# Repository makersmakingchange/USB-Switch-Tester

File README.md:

# USB SWITCH TESTER
The USB Switch Tester is used to test the functionality of an assistive switch with a 3.5 mm connection.

## More info at
- [Makers Making Change Assistive Device Library ](https://www.makersmakingchange.com/product/usb-switch-tester/01tJR000000690rYAA)

## How to Obtain a USB Switch Tester
### 1. Do it Yourself (DIY) or Do it Together (DIT)

This is an open-source assistive technology, so anyone is free to build it. All of the files and instructions required to build the USB Swtich Tester are contained within this repository. Refer to the Maker Checklist below.

### 2. Request a build of this device

If you would like to obtain a USB Switch Tester , you may submit a build request through the [MMC Library Page](https://www.makersmakingchange.com/product/usb-switch-tester/01tJR000000690rYAA). The requestor is responsible for the cost of materials and any shipping.

### 3. How to build this device for someone else

If you have the skills and equipment to build this device, and would like to donate your time to create the switch for someone who needs it, visit the [MMC Maker Wanted](https://makersmakingchange.com/maker-wanted/) section.

## Getting Started

### 1. Read the Makers Checklist

The Makers Checklist contains a list of tasks to complete to build the device.

### 2. Order the Off-The-Shelf Components

The [Bill of Materials](/Documentation/USB_Switch_Tester_BOM.xlsx) lists all of the parts and components required to build the USB Switch Tester. The main switch component needs to be ordered online. The rest of the off-the-shelf components are also online or may be available in smaller quantities at your local hardware store or dollar store.

### 3. Print the 3D Printable components

Print the top and bottom components of the case of the device. 

All of the files and individual print files can be in the [/Build_Files/3D_Printing_Files](/Build_Files/3D_Printing_Files/) folder.

### 4. Assemble the USB Switch Tester

Reference the [Assembly Guide](/Documentation/USB_Switch_Tester_Assembly_Guide.pdf) for the tools and steps required to build each portion.

## Files
### Documentation
| Document             | Version | Link |
|----------------------|---------|------|
| Design Rationale     | 1.0     | [USB_Switch_Tester_Design_Rationale](/Documentation/USB_Switch_Tester_Design_Rationale.pdf)     |
| Maker Checklist      | 1.0     | [USB_Switch_Tester_Checklist](/Documentation/USB_Switch_Tester_Maker_Checklist.pdf)     |
| Bill of Materials    | 1.0     | [USB_Switch_Tester_Bill_of_Materials](/Documentation/USB_Switch_Tester_BOM.xlsx)     |
| 3D Printing Guide    | 1.0     | [USB_Switch_Tester_3D_Printing_Guide](/Documentation/USB_Switch_Tester_3D_Printing_Guide.pdf)     |
| Assembly Guide       | 1.0     | [USB_Switch_Tester_Assembly_Guide](/Documentation/USB_Switch_Tester_Assembly_Guide.pdf)     |
| User Guide           | 1.0     | [USB_Switch_Tester_User_Guide](/Documentation/USB_Switch_Tester_User_Guide.pdf)    |
| Changelog            | 1.0     | [USB_Switch_Tester_Changelog](/Documentation/USB_Switch_Tester_Changelog.pdf)     |

### Design Files
 - [CAD Files](/Design_Files/CAD)
 - [PCB Design Files](/Design_Files/PCB)

### Build Files
 - [3D Printing Files](/Build_Files/3D_Printing_Files)
 - [PCB Gerber Files](/Build_Files/PCB_Files)

## Attribution
Designers:
 - Milad Hajihassan
 - Derrick Andrews

## License
Everything needed or used to design, make, test, or prepare the USB Switch Tester is licensed under the CERN 2.0 Weakly Reciprocal license <https://ohwr.org/project/cernohl/wikis/Documents/CERN-OHL-version-2> (CERN-OHL-W) . 

Accompanying material such as instruction manuals, videos, and other copyrightable works that are useful but not necessary to design, make, test, or prepare the USB Switch Tester are published under a Creative Commons Attribution-ShareAlike 4.0 license https://creativecommons.org/licenses/by-sa/4.0/ (CC BY-SA 4.0).

---
<!-- ABOUT MMC START -->

## About Makers Making Change

Makers Making Change is a program of [Neil Squire](https://www.neilsquire.ca/), a Canadian non-profit that uses technology, knowledge, and passion to empower people with disabilities.

Makers Making Change leverages the capacity of community based Makers, Disability Professionals and Volunteers to develop and deliver affordable Open Source Assistive Technologies.

 - Website: [www.MakersMakingChange.com](https://www.makersmakingchange.com/)
 - GitHub: [makersmakingchange](https://github.com/makersmakingchange)
 - Bluesky: [@makersmakingchange.bsky.social](https://bsky.app/profile/makersmakingchange.bsky.social)
 - Instagram: [@makersmakingchange](https://www.instagram.com/makersmakingchange)
 - Facebook: [makersmakechange](https://www.facebook.com/makersmakechange)
 - LinkedIn: [Neil Squire Society](https://www.linkedin.com/company/neil-squire-society/)
 - Thingiverse: [makersmakingchange](https://www.thingiverse.com/makersmakingchange/about)
 - Printables: [MakersMakingChange](https://www.printables.com/@MakersMakingChange)

### Contact Us
For technical questions, to get involved, or to share your experience we encourage you to [visit our website](https://www.makersmakingchange.com/) or [contact us](https://www.makersmakingchange.com/s/contact).
<!-- ABOUT MMC END -->

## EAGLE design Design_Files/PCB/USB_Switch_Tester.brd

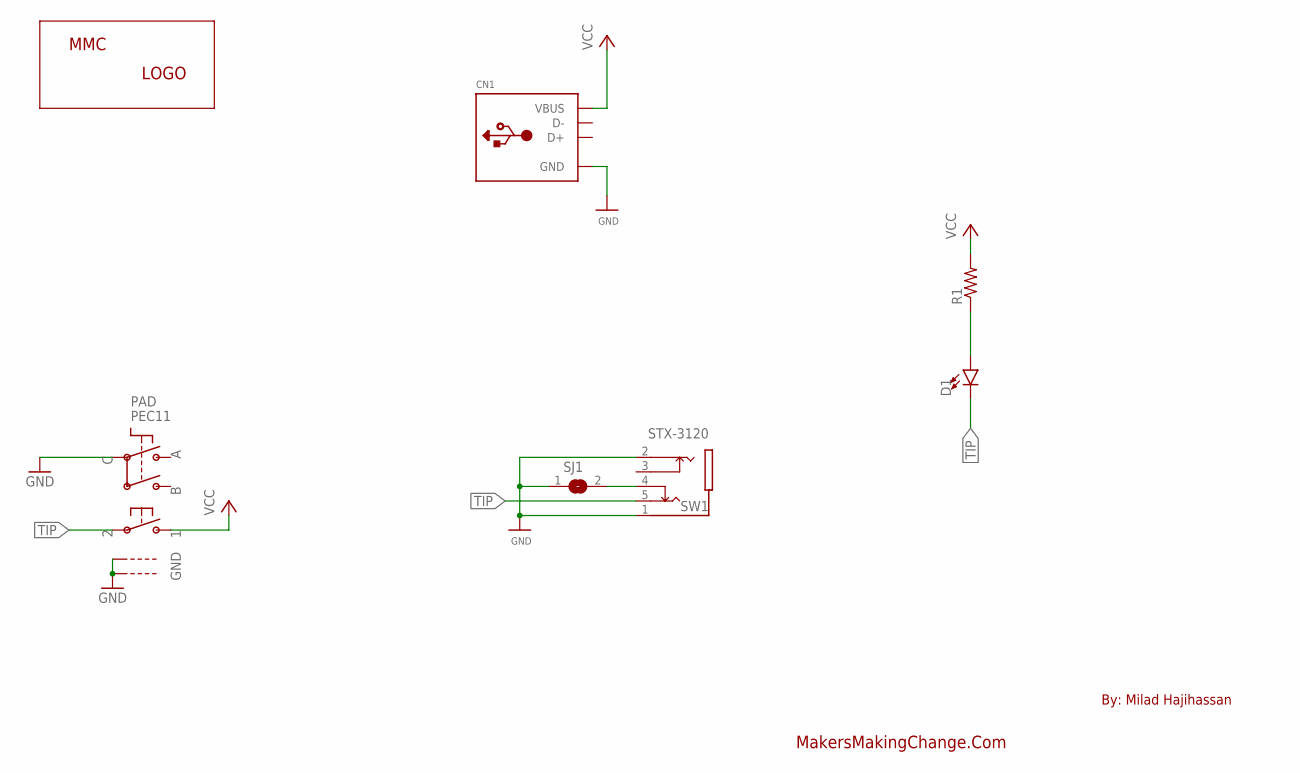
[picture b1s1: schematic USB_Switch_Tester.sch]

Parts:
CN1: MICROBUILDER_USB_TYPEAPCB; MICROBUILDER_USBA_PCB
D1: LED_5MM-5MM-RED; LED_5MM_RED
LABEL_LOGO: MMC_LOGO-XSM; MMC_X-SMALL_LOGO
PAD: PEC11; ADAFRUIT_ELECTROMECH_PEC11+SWITCH
R1: RESISTOR-US-0204/5; RESISTOR_0204/5
SJ1: SOLDERJUMPERREFLOW; SOLDERJUMPER_REFLOW
SW1: STX-3120; STX-3120-5B

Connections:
GND: CN1.GND, PAD.P$C, PAD.P$GND1, PAD.P$GND2, SJ1.1, SW1.1, SW1.2
unnamed: D1.A, R1.1
unnamed: SJ1.2, SW1.4
TIP: D1.K (C), PAD.P$2, SW1.5
VCC: CN1.VCC (VBUS), PAD.P$1, R1.2

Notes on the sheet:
By: Milad Hajihassan
MakersMakingChange.Com

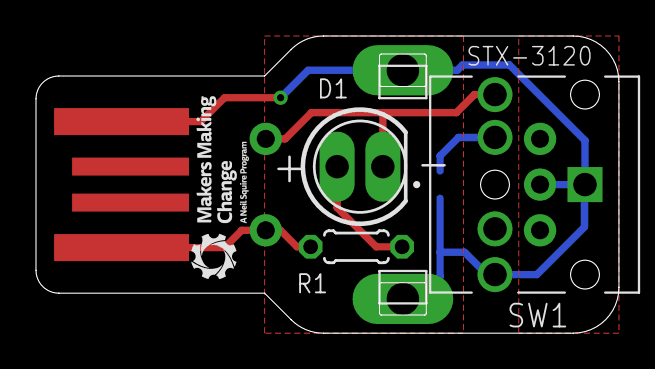
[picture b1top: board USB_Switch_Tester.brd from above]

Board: 2 copper layers, 32.4 x 16.5 mm, 7 parts (1 on the bottom side), 5 nets.

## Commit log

2022-12-22 First upload of files
2022-12-22 weird artifacts
2023-02-28 Updated PCB: Added MMC Logo
2023-04-27 Updated the enclosure design to simplify assembly process
2023-04-28 Updated assembly guide
2025-04-10 Add Update About MMC GitHub Action
2025-04-11 Update license
2025-04-11 Remove version from documentation file name
2025-04-12 Update About MMC Section
2026-01-05 Revise README with new links and project details
    Updated project information and links for the USB Switch Tester.
